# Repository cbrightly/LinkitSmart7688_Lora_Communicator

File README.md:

# LinkitSmart7688_Lora_Communicator
Kicad and gerber files to use Linkit Smart7688 Duo as a LORA Pager

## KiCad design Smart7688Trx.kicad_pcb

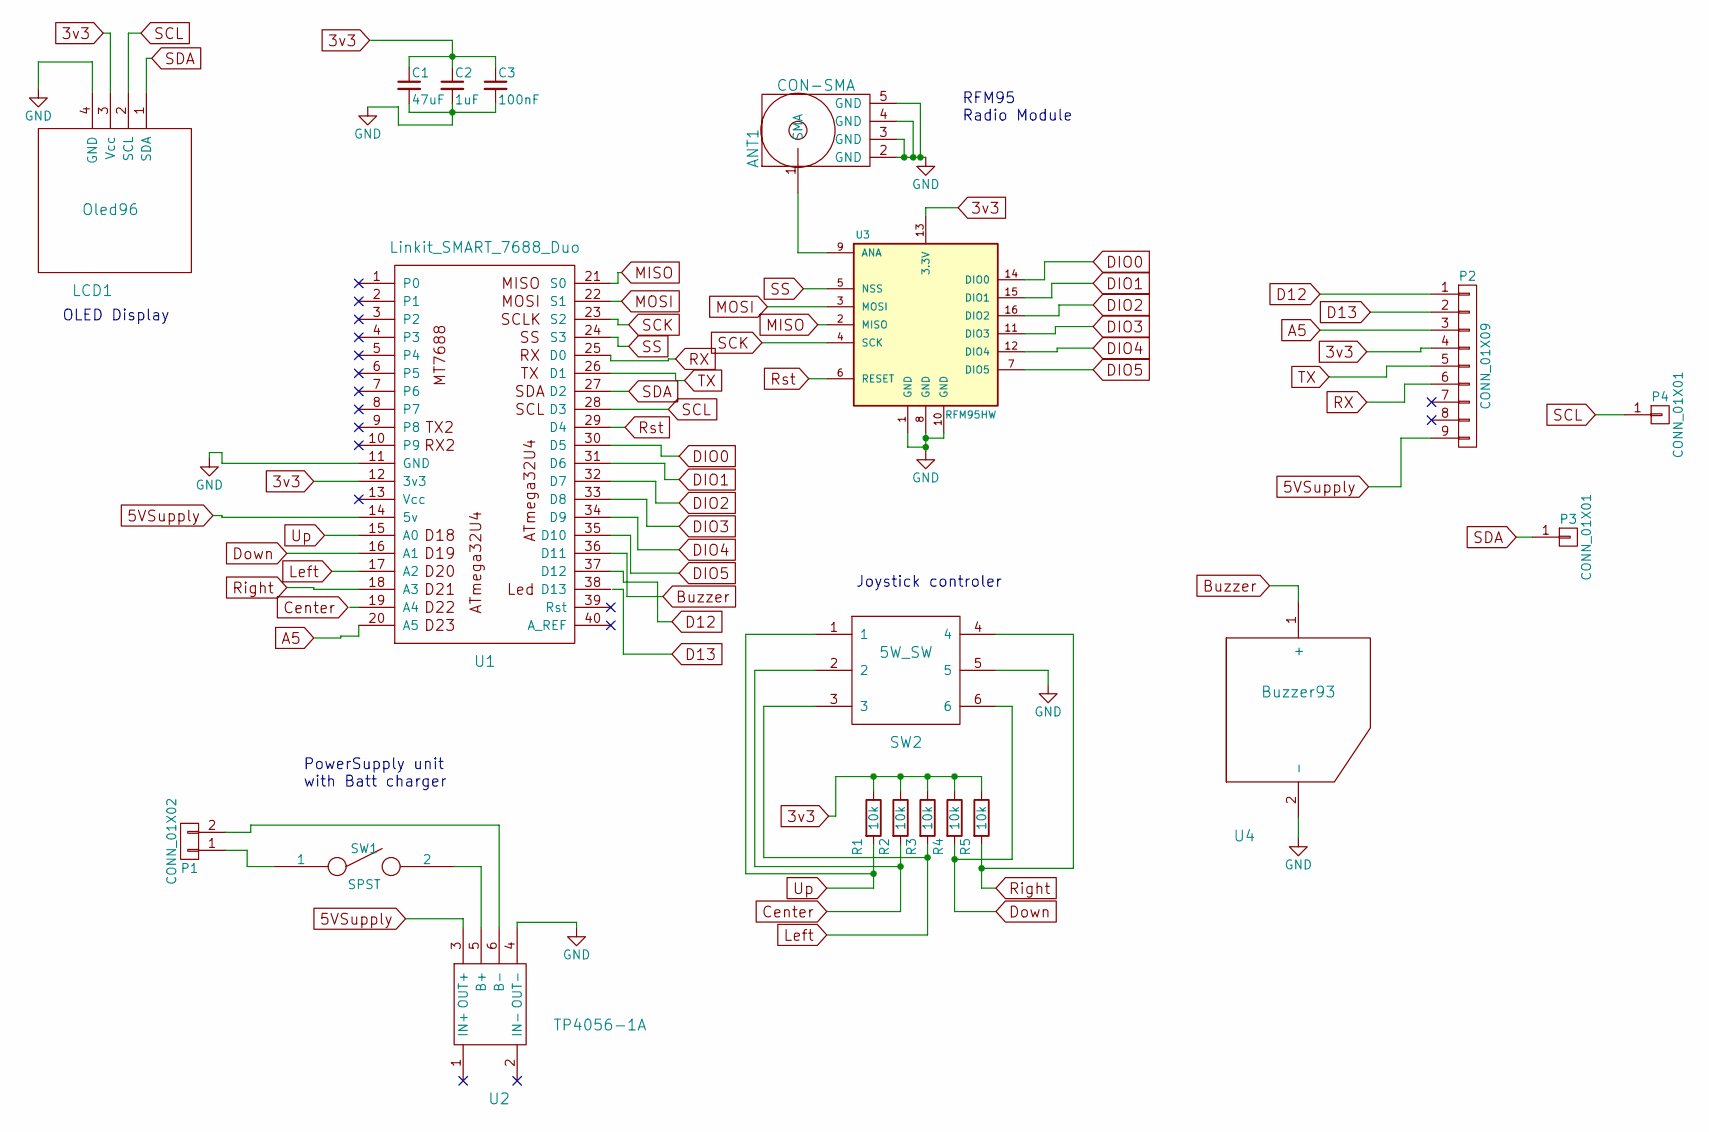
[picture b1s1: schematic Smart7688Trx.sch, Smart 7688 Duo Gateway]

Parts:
ANT1: CON-SMA; SMA_EDGE
C1: 47uF; C_1206_HandSoldering
C2: 1uF; C_1206_HandSoldering
C3: 100nF; C_1206_HandSoldering
LCD1: Oled96
P1: CONN_01X02; JST_EH_S02B-EH_02x2.50mm_Angled
P2: CONN_01X09; Socket_Strip_Straight_1x09_Pitch2.54mm
P3, P4: CONN_01X01; Socket_Strip_Straight_1x01_Pitch2.54mm
R1, R2, R3, R4, R5: 10k; R_1206_HandSoldering
SW1: SPST; SW_SPDT_PCM12
SW2: 5W_SW; 5WAY_sw
U1: Linkit_SMART_7688_Duo; SMART_7688_Duo
U2: TP4056-1A; TP4056-18650
U3: RFM95HW; RFM69HW_SMD_Handsoldering
U4: Buzzer93

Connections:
3v3: C1.1, C2.1, C3.1, LCD1.3 (Vcc), P2.4, R1.1, R2.1, R3.1, R4.1, R5.1, U1.12 (3v3), U3.13 (3.3V)
5VSupply: P2.9, U1.14 (5v), U2.3 (OUT+)
A5: P2.3, U1.20 (A5)
Buzzer: U1.36 (D11), U4.1 (+)
Center: R2.2, SW2.2; also elsewhere on the board
D12: P2.1, U1.37 (D12)
D13: P2.2
DIO0: U1.30 (D5), U3.14 (DIO0)
DIO1: U1.31 (D6), U3.15 (DIO1)
DIO2: U1.32 (D7), U3.16 (DIO2)
DIO3: U1.33 (D8), U3.11 (DIO3)
DIO4: U1.34 (D9), U3.12 (DIO4)
DIO5: U1.35 (D10), U3.7 (DIO5)
Down: R4.2, SW2.6, U1.16 (A1); also elsewhere on the board
GND: ANT1.2 (GND), ANT1.3 (GND), ANT1.4 (GND), ANT1.5 (GND), C1.2, C2.2, C3.2, LCD1.4 (GND), SW2.5, U1.11 (GND), U2.4 (OUT-), U3.1 (GND), U3.8 (GND), U3.10 (GND), U4.2 (-); also elsewhere on the board
Left: R3.2, SW2.3, U1.17 (A2); also elsewhere on the board
MISO: U1.21 (S0), U3.2 (MISO)
MOSI: U1.22 (S1), U3.3 (MOSI)
unnamed: ANT1.1 (SMA), U3.9 (ANA)
unnamed: P1.1, SW1.1
unnamed: P1.2, U2.6 (B-)
unnamed: SW1.2, U2.5 (B+)
RX: P2.6, U1.25 (D0)
Right: R5.2, SW2.4, U1.18 (A3); also elsewhere on the board
Rst: U1.29 (D4), U3.6 (RESET)
SCK: U1.23 (S2), U3.4 (SCK)
SCL: LCD1.2 (SCL), P4.1, U1.28 (D3)
SDA: LCD1.1 (SDA), P3.1, U1.27 (D2)
SS: U1.24 (S3), U3.5 (NSS)
TX: P2.5, U1.26 (D1)
Up: R1.2, SW2.1, U1.15 (A0); also elsewhere on the board

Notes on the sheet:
Joystick controler
RFM95 Radio Module
PowerSupply unit with Batt charger
OLED Display

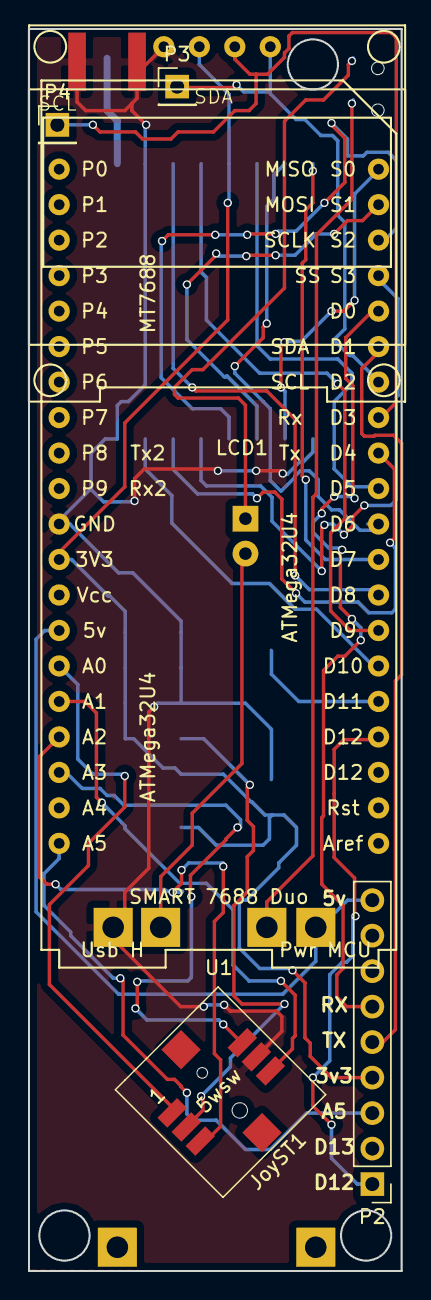
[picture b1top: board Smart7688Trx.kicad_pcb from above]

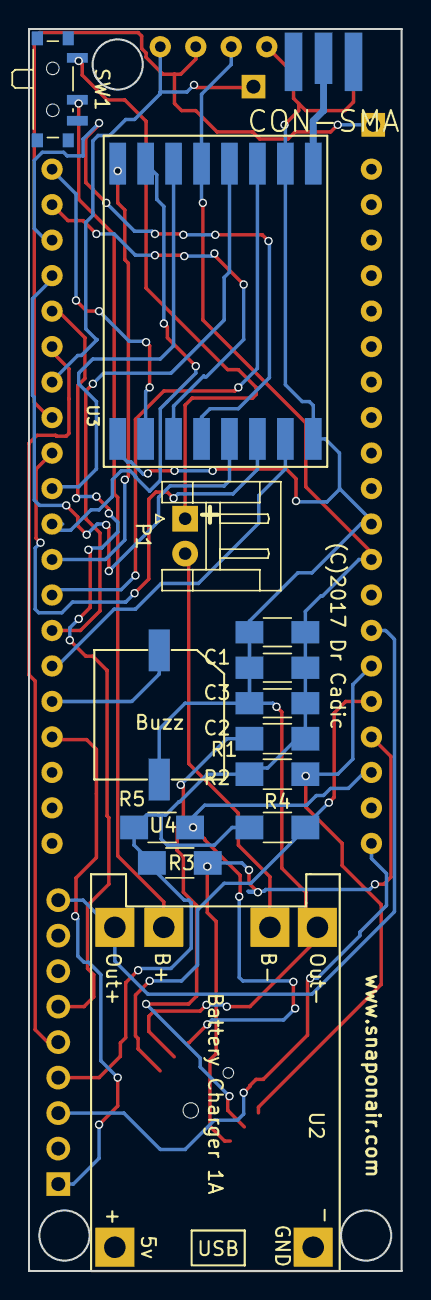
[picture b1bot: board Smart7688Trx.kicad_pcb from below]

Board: 2 copper layers, 26.7 x 88.9 mm, 20 parts (14 on the bottom side), 30 nets.

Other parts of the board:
JoyST1: 5W_SW; 5WAY_sw

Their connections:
Center: JoyST1.2; also elsewhere on the board
Down: JoyST1.6; also elsewhere on the board
GND: JoyST1.5; also elsewhere on the board
Left: JoyST1.3; also elsewhere on the board
Right: JoyST1.4; also elsewhere on the board
Up: JoyST1.1; also elsewhere on the board

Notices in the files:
Smart7688Trx.kicad_pcb:
(C)2017 Dr Cadic
